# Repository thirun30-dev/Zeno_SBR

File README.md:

🤖 ZENO — Self-Balancing Robot

<p align="center">
  <b>Balance Ideas Into Motion.</b><br>
  ESP32 • MPU9250 • PID Control • N20 Encoder Motors • TB6612FNG • Custom CAD/PCB • Web Dashboard
</p>

📌 About ZENO

ZENO is a compact two-wheeled self-balancing robot developed as a hands-on platform for embedded systems, feedback control, sensor fusion, motor control, mechanical design, PCB development, and robot–user interaction.

The robot uses an ESP32 DevKit V1 as the main controller, an MPU9250 IMU to estimate body tilt, and two N20 3 V 500 RPM geared DC motors with encoders driven by a TB6612FNG dual motor driver. A PID controller continuously calculates the correction required to keep the robot close to its calibrated upright angle.

The repository also contains the current mechanical design files, 3D-printable parts, a PCB placement/connectivity draft, individual hardware test programs, and the main balancing firmware.

✨ Key Features

Two-wheel real-time self-balancing

ESP32-based embedded control

MPU9250 accelerometer and gyroscope sensing

Complementary-filter angle estimation

PID balance control

N20 encoder motor drive

Serial-command control and PID tuning

IMU calibration routine

Forward, reverse, left, and right movement commands

Automatic motor shutdown beyond a configured fall angle

Modular two-layer mechanical chassis

Custom PCB development files

3D-printable motor cap, base, top deck, and threaded spacers

MAX7219 LED matrix hardware provision for expressive robot eyes

Web-dashboard concept for telemetry, visualization, control, and tuning

🧠 Control Architecture

MPU9250 IMU
    │
    ▼
Accelerometer + Gyroscope
    │
    ▼
Complementary Filter
    │
    ▼
Estimated Pitch Angle
    │
    ▼
Target Angle − Current Angle
    │
    ▼
PID Controller
    │
    ▼
Motor PWM + Direction
    │
    ▼
TB6612FNG Motor Driver
    │
    ▼
N20 Encoder Motors
    │
    └──────── Encoder Feedback ────────┐
                                      │
                                      ▼
                                 ESP32 Control

The current firmware uses starting PID values of:

Kp = 22.0
Ki = 0.0
Kd = 0.85

These are starting values only and must be tuned for the final ZENO mechanical configuration.

🔩 Main Hardware

Component

Specification

Main controller

ESP32 DevKit V1

IMU

MPU9250

Motor driver

TB6612FNG

Motors

2 × N20 3 V 500 RPM geared DC motors

Feedback

Motor encoder signals

Robot eyes

2 × MAX7219 8×8 LED matrix modules

Battery system

Protected 2S battery pack

Nominal battery voltage

7.4 V

Fully charged voltage

8.4 V

ESP32 / display rail

Regulated 5 V

Motor rail

Regulated nominal 3 V

Logic rail

ESP32 3.3 V

PCB outline

Approx. 130 × 77 mm

The motor supply and regulator current capability must be selected using the measured motor stall current. Do not power the stated 3 V motors directly from the raw 2S battery.

🔌 ESP32 Pin Mapping

MPU9250

Signal

ESP32

SDA

GPIO 22

SCL

GPIO 23

I2C address

0x68

TB6612FNG

Signal

ESP32

PWMA

GPIO 25

AIN1

GPIO 26

AIN2

GPIO 27

STBY

GPIO 32

BIN1

GPIO 14

BIN2

GPIO 13

PWMB

GPIO 33

Encoder Input Currently Used by Main Firmware

Signal

ESP32

Encoder A

GPIO 19

Encoder B

GPIO 18

🎮 Serial Commands

The main firmware supports interactive control through the Arduino Serial Monitor.

Command

Function

C

Calibrate IMU

B

Enable balancing

S

Stop balancing

F

Move forward

R

Move backward

L

Turn left

T

Turn right

X

Stop movement

P

Print PID values

I

Increase Kp

i

Decrease Kp

O

Increase Ki

o

Decrease Ki

D

Increase Kd

d

Decrease Kd

⚖️ Calibration and Balancing

Before balancing, place ZENO in the intended upright position and send:

C

The firmware calibrates the IMU and establishes the angle reference. Once calibration is complete, balancing can be enabled with:

B

The robot continuously compares the current tilt with the target angle and applies motor corrections. The current firmware contains a 40° fall-angle safety threshold; when the robot exceeds this angle, motor drive is stopped to reduce uncontrolled motion.

🖥️ ZENO Web Dashboard

ZENO is also being developed with a dedicated web dashboard for a more intuitive robot-monitoring and control experience. The dashboard is intended to complement the ESP32 firmware and Serial Monitor rather than replace firmware-side safety logic.

Planned / Supported Dashboard Areas

Animated 3D ZENO introduction

Light and dark themes

Robot connection state

Balance state

Live pitch / tilt angle

Target angle and PID error

Kp, Ki, and Kd visualization

Left and right motor output

Encoder count / wheel-speed telemetry

IMU acceleration and angular velocity

Battery / power status

Calibration control

Start / stop balancing

Manual movement controls

Emergency-stop interface

Real-time telemetry graphs

PID tuning controls

3D robot orientation visualization

Dashboard Data Flow

ZENO Hardware
     │
     ▼
ESP32 Firmware
     │
     ├── IMU Data
     ├── PID Data
     ├── Encoder Data
     ├── Motor Output
     └── System Status
            │
            ▼
     Wi-Fi / WebSocket
            │
            ▼
      ZENO Dashboard
            │
      ┌─────┴─────┐
      ▼           ▼
 Telemetry      Control

Repository note: the uploaded repository snapshot currently contains the firmware, CAD/3D files, PCB draft, and image assets. The dashboard source is not yet included in this snapshot. Add it under a dedicated Dashboard/ or dashboard/ directory when integrating the web application.

🧱 Mechanical Design

ZENO uses a modular two-layer structure.

Base Layer

The lower section is intended to carry:

N20 motors

Wheels

Battery / battery holder

Motor mounting parts

Structural mounting points

Top Layer

The upper section is intended to carry:

Custom PCB

ESP32 DevKit V1

TB6612FNG

MPU9250

Display modules

Calibration button

The repository includes printable and editable mechanical files for the robot base, top deck, N20 motor cap, deck spacers, and assembly references.

🧩 Repository Structure

Zeno_SBR/
│
├── 3D/
│   ├── 3D print/
│   │   ├── ZENO_base.stl
│   │   ├── top_deck.stl
│   │   ├── N20_single_cap_1.STL
│   │   └── deck_spacer_50mm_M3_threaded.stl
│   │
│   ├── ZENO_Base_Mounting_Holes/
│   ├── ZENO_N20_Single_Cap/
│   ├── ZENO_PCB_Draft/
│   └── ZENO_Top_Layer/
│
├── Code/
│   ├── Motor_Test/
│   │   └── Motor_Test.ino
│   ├── MPU9250/
│   │   └── MPU9250.ino
│   └── ZENO_code/
│       └── ZENO_code.ino
│
└── ZENO.png

After adding the web application, a recommended extension is:

├── Dashboard/
│   ├── src/
│   ├── public/
│   ├── package.json
│   └── README.md

📁 Important Repository Files

Code/Motor_Test/Motor_Test.ino

Used to verify TB6612FNG wiring and basic motor direction/control independently of the balancing loop.

Code/MPU9250/MPU9250.ino

Used to test MPU9250 communication, calibration, and orientation measurement separately.

Code/ZENO_code/ZENO_code.ino

Current integrated ZENO balancing firmware containing IMU acquisition, calibration, complementary filtering, PID calculations, motor control, encoder input, serial commands, and fall protection.

3D/3D print/

Contains the primary STL files intended for fabrication/3D printing.

3D/ZENO_PCB_Draft/

Contains the current KiCad placement and connectivity draft.

⚠️ PCB Development Status

The included ZENO Rev A PCB is a placement/connectivity draft and is currently marked:

UNROUTED — NOT FOR FABRICATION

The PCB files must be fully verified before manufacturing. Required work includes:

Verify physical module footprints and pin order

Confirm motor and encoder electrical requirements

Verify ESP32 footprint spacing

Verify connector families and orientation

Add routing, vias, and copper zones

Add a continuous ground reference

Check ESP32 antenna clearance

Verify motor-current trace width

Complete schematic/ERC verification

Run KiCad DRC

Generate and inspect Gerbers only after validation

Do not submit the current PCB draft directly for fabrication.

🚀 Running the Firmware

Install the ESP32 board package in the Arduino IDE.

Connect the ESP32 DevKit V1.

Open:

Code/ZENO_code/ZENO_code.ino

Select the appropriate ESP32 board and COM/serial port.

Compile and upload the firmware.

Open Serial Monitor.

Keep the robot supported safely with wheels free during initial testing.

Send C to calibrate.

Verify angle direction and motor direction before enabling balance mode.

Tune PID values gradually for the final mechanical build.

🧪 Recommended Testing Sequence

1. Verify regulated power rails
        ↓
2. Test MPU9250 communication
        ↓
3. Run Motor_Test.ino
        ↓
4. Confirm both motor directions
        ↓
5. Verify encoder response
        ↓
6. Upload integrated ZENO firmware
        ↓
7. Calibrate IMU
        ↓
8. Verify tilt-angle direction
        ↓
9. Test balancing while physically supported
        ↓
10. Tune PID parameters
        ↓
11. Perform controlled free-balance tests
        ↓
12. Integrate live dashboard telemetry

🛠️ Development Roadmap

Mechanical base design

Top deck design

N20 motor mounting design

M3 threaded spacer design

MPU9250 test firmware

Motor test firmware

Integrated balancing firmware

Serial-based PID adjustment

Fall-angle protection

Initial PCB placement/connectivity draft

Tune PID on the completed mechanical robot

Validate both motor encoders independently

Complete and route PCB

Fabricate and test custom PCB

Integrate MAX7219 eye animations into main firmware

Add Wi-Fi/WebSocket telemetry

Add dashboard source to repository

Connect dashboard to live ESP32 data

Add battery monitoring

Add OTA firmware updates

Add advanced motion/position control

🎯 Applications and Learning Outcomes

ZENO can be used to explore:

Self-balancing robotics

Inverted-pendulum control

Embedded C/C++ programming

ESP32 development

PID control

Sensor fusion

IMU calibration

DC motor control

Encoder feedback

PCB design

CAD and 3D printing

Power-system integration

Web-based robot telemetry

Human–robot interaction

⚠️ Safety

ZENO contains moving motors and a rechargeable battery system. During development:

Verify regulator outputs before connecting electronics.

Use a protected battery pack.

Keep a physical power-disconnect method available.

Do not test balancing near edges or fragile objects.

Support the chassis during initial PID tuning.

Confirm motor direction before enabling closed-loop balancing.

Do not treat a web-based emergency-stop button as a substitute for hardware power isolation.

📈 Project Status

Active Development

The mechanical design, test firmware, integrated balancing firmware, and initial PCB draft are present in this repository. PID tuning, PCB completion, display integration, wireless telemetry, and web-dashboard integration remain active development areas.

📜 Disclaimer

ZENO is an educational and experimental robotics project. Hardware dimensions, electrical connections, PCB footprints, power-system limits, PID parameters, and software should be independently verified before fabrication or operation.

🤝 Contributions

Suggestions, improvements, testing feedback, and contributions are welcome as the ZENO platform develops.

<p align="center">
  <b>ZENO</b><br>
  <i>Balance Ideas Into Motion.</i>
</p>

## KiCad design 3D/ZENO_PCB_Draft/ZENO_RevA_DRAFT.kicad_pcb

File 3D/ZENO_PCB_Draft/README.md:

# ZENO Rev A — placement and connectivity draft

**UNROUTED. NOT FOR FABRICATION.** No Gerbers or fabrication release are included. Native KiCad loading and DRC were not available in this environment. Open the board directly in KiCad PCB Editor. Nets provide ratsnest connections; there is no graphical .kicad_sch schematic. The XML netlist is supplementary.

## Mechanical plan
130 × 77 × 1.6 mm, two copper layers. Front is y=77; rear is y=0. Proposed 3.2 mm mounting holes: (5,5), (125,5), (5,72), (125,72) mm. Hole spacing 120 × 67 mm is provisional, not matched to chassis. Module sockets use 1 mm drills and 1.7 mm pads provisionally. No connector body courtyards or final housing geometry have been validated. The preview is a placement drawing, not a rendering of a finished routed PCB.

## Electrical decisions
External regulated +5 V enters J7; external regulated nominal 3 V motor power enters J8. Raw 2S battery must not enter either connector. Use upstream protection and regulator current capacity appropriate to measured loads. Do not simultaneously connect external 5 V and USB until the actual DevKit power-path isolation is checked. VM and +5 V share ground but are not connected together. TB6612 logic VCC is +3V3. Check driver suitability against motor stall current and thermal conditions; no stall-current validation has been performed.

Encoder supply is provisionally 3.3 V. If encoder requires 5 V, redesign supply and level conversion before connection. GPIO34/35/36/39 are input-only; external pull-up footprints are provided. Do not infer cable pin order from colours. Motor minus is a bridge output, not ground.

Displays use three 5 V SN74AHCT125 buffer channels. Eye 1 DOUT must return through J5 to eye 2 DIN at J4. Both displays share CLK and CS. This additional return connection is required for independent eyes in a daisy chain. Alternatively wire module-to-module and revise the harness accordingly.

Calibration: J6 pins 1 COM/GND, 2 NO/GPIO4, 3 LED+/5V, 4 LED-/GND. NC unused. LED continuously on with power if purchased LED supports 5 V. Firmware must debounce and allow calibration only when stationary with motor outputs disabled. This button is not a battery disconnect or emergency stop.

IMU: AD0 low selects 0x68 for compatible devices; NCS held high for I2C, FSYNC low. EDA/ECL/INT unused. Verify sensor identity, VCC regulator dropout, and bus pull-ups on actual board. Optional carrier I2C pull-ups R7/R8 are DNP by default.

## Before routing and fabrication
1. Measure ESP32 row spacing (assumed 25.4 mm), TB6612 row spacing (assumed 15.24 mm), and IMU pitch (assumed 2.54 mm). Confirm module face/orientation against every net, especially TB6612 photograph.
2. Identify exact six-pin JST family, pitch, mating PCB header and cable orientation. Current J1/J2 pads are 2.0 mm placeholders, not validated connector footprints.
3. Measure standoffs and switch chassis clearance; confirm motor/encoder voltage and stall current.
4. Replace provisional footprints with verified body outlines/courtyards, add actual ESP32 antenna copper/component keepout on both sides and maintain USB access.
5. Route motor paths short and wide, away from IMU and I2C; size copper for measured current and copper weight. Provide ground plane and local decoupling. This draft has ZERO tracks, vias, zones, or enforced keepouts.
6. Create/verify graphical schematic and ERC, route every net, then run KiCad DRC and review fabrication outputs. Print footprint page at 1:1 and physically test-fit before ordering.

## Sources
- ESP32: https://www.espressif.com/sites/default/files/documentation/esp32_datasheet_en.pdf
- TB6612FNG: https://www.sparkfun.com/datasheets/Robotics/TB6612FNG.pdf
- MAX7219: https://www.analog.com/media/en/technical-documentation/data-sheets/MAX7219-MAX7221.pdf
- SN74AHCT125: https://www.ti.com/lit/ds/symlink/sn74ahct125.pdf
Module pin labels were taken from user-supplied photographs; module dimensions were not supplied.

## Parts and pad assignments

### U1 — ESP32_DEVKIT_V1_30PIN_ASSUMED
Component-side top view, USB at rear. Left row VIN..EN; right row 3V3..D23. 25.4 mm row spacing and 2.54 mm pitch ASSUMED; compare physical board before fabrication.

| Pad | Net |
|---:|---|
| 1 | +5V |
| 2 | GND |
| 3 | DISP_DIN |
| 4 | NC_D12 |
| 5 | PWMB |
| 6 | AIN2 |
| 7 | AIN1 |
| 8 | PWMA |
| 9 | DISP_CS |
| 10 | DISP_CLK |
| 11 | ENC_L_B |
| 12 | ENC_L_A |
| 13 | ENC_R_B |
| 14 | ENC_R_A |
| 15 | NC_EN |
| 16 | +3V3 |
| 17 | GND |
| 18 | NC_D15 |
| 19 | NC_D2 |
| 20 | CAL |
| 21 | NC_RX2 |
| 22 | NC_TX2 |
| 23 | NC_D5 |
| 24 | BIN1 |
| 25 | BIN2 |
| 26 | SDA |
| 27 | NC_RX0 |
| 28 | NC_TX0 |
| 29 | SCL |
| 30 | STBY |

### U2 — TB6612FNG_MODULE_ASSUMED
Pin sequence from supplied labelled face; verify which face is upward when plugged in. 15.24 mm row spacing ASSUMED.

| Pad | Net |
|---:|---|
| 1 | PWMA |
| 2 | AIN2 |
| 3 | AIN1 |
| 4 | STBY |
| 5 | BIN1 |
| 6 | BIN2 |
| 7 | PWMB |
| 8 | GND |
| 9 | VM |
| 10 | +3V3 |
| 11 | GND |
| 12 | M_L_P |
| 13 | M_L_N |
| 14 | M_R_N |
| 15 | M_R_P |
| 16 | GND |

### U3 — MPU9250_6500_MODULE_ASSUMED
2.54 mm pitch ASSUMED; AD0 low, NCS high, FSYNC low. Module VCC regulator/dropout must be checked; sensor identity unconfirmed.

| Pad | Net |
|---:|---|
| 1 | +3V3 |
| 2 | GND |
| 3 | SCL |
| 4 | SDA |
| 5 | NC_EDA |
| 6 | NC_ECL |
| 7 | GND |
| 8 | NC_INT |
| 9 | +3V3 |
| 10 | GND |

### J1 — LEFT_MOTOR_JST_PH_6_ASSUMED
2.0 mm pitch PLACEHOLDER, not validated JST housing. Cable pin order is proposed, not measured.

| Pad | Net |
|---:|---|
| 1 | M_L_N |
| 2 | M_L_P |
| 3 | +3V3 |
| 4 | GND |
| 5 | ENC_L_A |
| 6 | ENC_L_B |

### J2 — RIGHT_MOTOR_JST_PH_6_ASSUMED
Same assumptions as J1; encoder supply and logic must support 3.3 V.

| Pad | Net |
|---:|---|
| 1 | M_R_N |
| 2 | M_R_P |
| 3 | +3V3 |
| 4 | GND |
| 5 | ENC_R_A |
| 6 | ENC_R_B |

### J3 — EYE_INPUT_5PIN

| Pad | Net |
|---:|---|
| 1 | +5V |
| 2 | GND |
| 3 | DIN_5V |
| 4 | CS_5V |
| 5 | CLK_5V |

### J4 — EYE_INPUT_5PIN

| Pad | Net |
|---:|---|
| 1 | +5V |
| 2 | GND |
| 3 | CHAIN_DOUT |
| 4 | CS_5V |
| 5 | CLK_5V |

### J5 — EYE1_DOUT_RETURN
Connect eye 1 output DOUT here. J4 DIN gets this net, never ESP32 input.

| Pad | Net |
|---:|---|
| 1 | CHAIN_DOUT |
| 2 | GND |

### J6 — REAR_CAL_BUTTON
COM,NO,LED+,LED-. NC unused. Actual switch terminals must be identified.

| Pad | Net |
|---:|---|
| 1 | GND |
| 2 | CAL |
| 3 | +5V |
| 4 | GND |

### J7 — REGULATED_5V_INPUT
External regulated 5 V only; no raw battery. Fuse and reverse-polarity protection upstream.

| Pad | Net |
|---:|---|
| 1 | +5V |
| 2 | GND |

### J8 — REGULATED_MOTOR_INPUT
External regulated nominal 3 V for stated 3 V motors. Supply/driver current suitability pending stall current.

| Pad | Net |
|---:|---|
| 1 | VM |
| 2 | GND |

### U4 — SN74AHCT125N_DIP14
PCB pad numbering is explicit DIP numbering. 5 V supply, three channels active, fourth disabled.

| Pad | Net |
|---:|---|
| 1 | GND |
| 2 | DISP_DIN |
| 3 | DIN_5V |
| 4 | GND |
| 5 | DISP_CS |
| 6 | CS_5V |
| 7 | GND |
| 14 | +5V |
| 13 | +5V |
| 12 | GND |
| 11 | NC_BUF_OUT |
| 10 | GND |
| 9 | DISP_CLK |
| 8 | CLK_5V |

### R1 — 10k
Encoder pull-ups populate only for verified compatible encoder outputs.

| Pad | Net |
|---:|---|
| 1 | ENC_L_A |
| 2 | +3V3 |

### R2 — 10k
Encoder pull-ups populate only for verified compatible encoder outputs.

| Pad | Net |
|---:|---|
| 1 | ENC_L_B |
| 2 | +3V3 |

### R3 — 10k
Encoder pull-ups populate only for verified compatible encoder outputs.

| Pad | Net |
|---:|---|
| 1 | ENC_R_A |
| 2 | +3V3 |

### R4 — 10k
Encoder pull-ups populate only for verified compatible encoder outputs.

| Pad | Net |
|---:|---|
| 1 | ENC_R_B |
| 2 | +3V3 |

### R5 — 10k
Encoder pull-ups populate only for verified compatible encoder outputs.

| Pad | Net |
|---:|---|
| 1 | CAL |
| 2 | +3V3 |

### R6 — 10k_STBY_PULLDOWN

| Pad | Net |
|---:|---|
| 1 | STBY |
| 2 | GND |

### C1 — 100nF

| Pad | Net |
|---:|---|
| 1 | +5V |
| 2 | GND |

### C2 — 100nF

| Pad | Net |
|---:|---|
| 1 | +3V3 |
| 2 | GND |

### C3 — 100nF

| Pad | Net |
|---:|---|
| 1 | +3V3 |
| 2 | GND |

### C4 — 100nF

| Pad | Net |
|---:|---|
| 1 | VM |
| 2 | GND |

### C5 — 470uF_10V
Polarized: pad 1 positive; 8 mm diameter placeholder.

| Pad | Net |
|---:|---|
| 1 | VM |
| 2 | GND |

### C6 — 220uF_10V
Polarized: pad 1 positive; 8 mm diameter placeholder.

| Pad | Net |
|---:|---|
| 1 | +5V |
| 2 | GND |

### R7 — 4k7_DNP
Optional I2C pull-up; normally DNP if module already provides pull-ups to 3.3 V.

| Pad | Net |
|---:|---|
| 1 | SDA |
| 2 | +3V3 |

### R8 — 4k7_DNP
Optional I2C pull-up; normally DNP if module already provides pull-ups to 3.3 V.

| Pad | Net |
|---:|---|
| 1 | SCL |
| 2 | +3V3 |

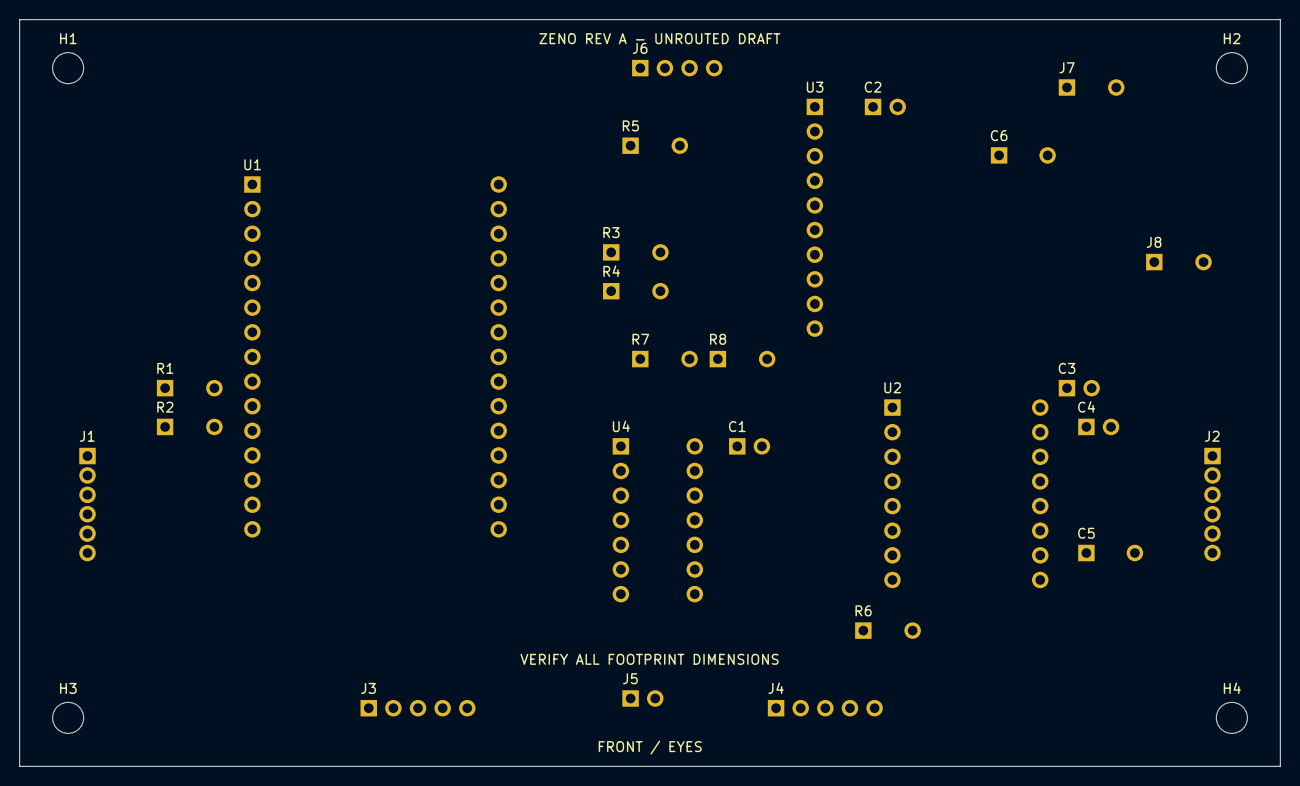
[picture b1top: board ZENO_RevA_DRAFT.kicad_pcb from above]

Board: 2 copper layers, 130.0 x 77.0 mm, 30 parts (0 on the bottom side), 29 nets, no tracks yet.

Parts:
C1, C2, C3, C4: 100nF
C5: 470uF_10V
C6: 220uF_10V
H1, H2, H3, H4: M3_NPTH
J1: LEFT_MOTOR_JST_PH_6_ASSUMED
J2: RIGHT_MOTOR_JST_PH_6_ASSUMED
J3, J4: EYE_INPUT_5PIN
J5: EYE1_DOUT_RETURN
J6: REAR_CAL_BUTTON
J7: REGULATED_5V_INPUT
J8: REGULATED_MOTOR_INPUT
R1, R2, R3, R4, R5: 10k
R6: 10k_STBY_PULLDOWN
R7, R8: 4k7_DNP
U1: ESP32_DEVKIT_V1_30PIN_ASSUMED
U2: TB6612FNG_MODULE_ASSUMED
U3: MPU9250_6500_MODULE_ASSUMED
U4: SN74AHCT125N_DIP14

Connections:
+3V3: C2.1, C3.1, J1.3, J2.3, R1.2, R2.2, R3.2, R4.2, R5.2, R7.2, R8.2, U1.16, U2.10, U3.1, U3.9
+5V: C1.1, C6.1, J3.1, J4.1, J6.3, J7.1, U1.1, U4.13, U4.14
AIN1: U1.7, U2.3
AIN2: U1.6, U2.2
BIN1: U1.24, U2.5
BIN2: U1.25, U2.6
CAL: J6.2, R5.1, U1.20
CHAIN_DOUT: J4.3, J5.1
CLK_5V: J3.5, J4.5, U4.8
CS_5V: J3.4, J4.4, U4.6
DIN_5V: J3.3, U4.3
DISP_CLK: U1.10, U4.9
DISP_CS: U1.9, U4.5
DISP_DIN: U1.3, U4.2
ENC_L_A: J1.5, R1.1, U1.12
ENC_L_B: J1.6, R2.1, U1.11
ENC_R_A: J2.5, R3.1, U1.14
ENC_R_B: J2.6, R4.1, U1.13
GND: C1.2, C2.2, C3.2, C4.2, C5.2, C6.2, J1.4, J2.4, J3.2, J4.2, J5.2, J6.1, J6.4, J7.2, J8.2, R6.2, U1.2, U1.17, U2.8, U2.11, U2.16, U3.2, U3.7, U3.10, U4.1, U4.4, U4.7, U4.10, U4.12
M_L_N: J1.1, U2.13
M_L_P: J1.2, U2.12
M_R_N: J2.1, U2.14
M_R_P: J2.2, U2.15
PWMA: U1.8, U2.1
PWMB: U1.5, U2.7
SCL: R8.1, U1.29, U3.3
SDA: R7.1, U1.26, U3.4
STBY: R6.1, U1.30, U2.4
VM: C4.1, C5.1, J8.1, U2.9

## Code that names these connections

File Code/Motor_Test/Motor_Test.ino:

/*
  ZENO - ESP32 + TB6612FNG Motor Test

  Serial Monitor:
    Baud rate: 115200
    Line ending: Newline or Both NL & CR

  Commands:
    F or FORWARD  -> Both wheels forward
    B or BACKWARD -> Both wheels backward
    S or STOP     -> Stop motors
    H or HELP     -> Show commands

  Motors automatically stop after 2 seconds.
  No additional libraries required.
*/

#include <Arduino.h>

constexpr uint8_t AIN1 = 25;
constexpr uint8_t AIN2 = 26;
constexpr uint8_t PWMA = 27;

constexpr uint8_t BIN1 = 32;
constexpr uint8_t BIN2 = 33;
constexpr uint8_t PWMB = 14;

constexpr uint8_t STBY = 13;

// Mirrored motors often require opposite electrical directions.
// Change the corresponding value if a wheel rotates the wrong way.
constexpr bool LEFT_REVERSED  = false;
constexpr bool RIGHT_REVERSED = true;

constexpr unsigned long RUN_TIME_MS = 2000;

bool motorsRunning = false;
unsigned long motorStartTime = 0;

char commandBuffer[32];
size_t commandLength = 0;
bool commandOverflow = false;

void stopMotors() {
  digitalWrite(STBY, LOW);

  digitalWrite(PWMA, LOW);
  digitalWrite(PWMB, LOW);

  digitalWrite(AIN1, LOW);
  digitalWrite(AIN2, LOW);
  digitalWrite(BIN1, LOW);
  digitalWrite(BIN2, LOW);

  motorsRunning = false;
}

void setDirection(uint8_t in1, uint8_t in2,
                  bool forward, bool reversed) {
  bool direction = forward != reversed;

  digitalWrite(in1, direction ? HIGH : LOW);
  digitalWrite(in2, direction ? LOW : HIGH);
}

void runMotors(bool forward) {
  // Disable the driver before changing direction.
  stopMotors();
  delay(20);

  setDirection(AIN1, AIN2, forward, LEFT_REVERSED);
  setDirection(BIN1, BIN2, forward, RIGHT_REVERSED);

  // Constant HIGH enables full output; this test does not use PWM.
  digitalWrite(PWMA, HIGH);
  digitalWrite(PWMB, HIGH);
  digitalWrite(STBY, HIGH);

  motorStartTime = millis();
  motorsRunning = true;

  Serial.println(forward
    ? "FORWARD: running for 2 seconds."
    : "BACKWARD: running for 2 seconds.");
}

void printHelp() {
  Serial.println();
  Serial.println("=== ZENO MOTOR TEST ===");
  Serial.println("F / FORWARD  : Move forward");
  Serial.println("B / BACKWARD : Move backward");
  Serial.println("S / STOP     : Stop");
  Serial.println("H / HELP     : Show commands");
  Serial.println("Automatic stop: 2 seconds");
  Serial.println("Use Newline or Both NL & CR.");
  Serial.println();
}

void processCommand() {
  commandBuffer[commandLength] = '\0';

  String command(commandBuffer);
  command.trim();
  command.toUpperCase();

  if (command == "F" || command == "FORWARD") {
    runMotors(true);
  } else if (command == "B" || command == "BACKWARD") {
    runMotors(false);
  } else if (command == "S" || command == "STOP") {
    stopMotors();
    Serial.println("STOPPED.");
  } else if (command == "H" || command == "HELP") {
    printHelp();
  } else if (command.length() > 0) {
    stopMotors();
    Serial.println("Unknown command. Motors stopped. Enter F, B or S.");
  }
}

void setup() {
  // Keep the driver disabled during initialization.
  pinMode(STBY, OUTPUT);
  digitalWrite(STBY, LOW);

  pinMode(AIN1, OUTPUT);
  pinMode(AIN2, OUTPUT);
  pinMode(PWMA, OUTPUT);

  pinMode(BIN1, OUTPUT);
  pinMode(BIN2, OUTPUT);
  pinMode(PWMB, OUTPUT);

  stopMotors();

  Serial.begin(115200);
  printHelp();
}

void loop() {
  if (motorsRunning &&
      millis() - motorStartTime >= RUN_TIME_MS) {
    stopMotors();
    Serial.println("AUTO STOP: 2-second test completed.");
  }

  // Read without blocking the automatic stop timer.
  if (Serial.available() > 0) {
    char received = Serial.read();

    if (received == '\n' || received == '\r') {
      if (commandOverflow) {
        Serial.println("Command too long. Motors stopped.");
      } else if (commandLength > 0) {
        processCommand();
      }

      commandLength = 0;
      commandOverflow = false;
    } else if (!commandOverflow) {
      if (commandLength < sizeof(commandBuffer) - 1) {
        commandBuffer[commandLength++] = received;
      } else {
        stopMotors();
        commandOverflow = true;
      }
    }
  }
}
